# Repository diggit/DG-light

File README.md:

# DG-light

Lightweight module to iluminate various flying discs. (frisbee, DiscGolf,...? )

## Hardware

Kept simple and lightweight as possible. Only: MCU, leds, button, passives.
- **MCU**: **ATMEGA8A**
- **LEDs**:
 - 16x 5mm edge oriented LEDs
 - 1x SMD status LED
- **Buttons**:
 - user button (all settings)
 - reset button (wake from power off)

## V1
Proof of concept. Partialy worked.
### problems:
- **SW**: needed recalibration often (changing surfaces like: grass and asphalt caused capacity changes)
- **HW**:
 - missing charging port 
 - missing battery connect jumper
 - ISP inder battery
*sensitive to palm under electronics -> used as another control element (reset after pickup)*

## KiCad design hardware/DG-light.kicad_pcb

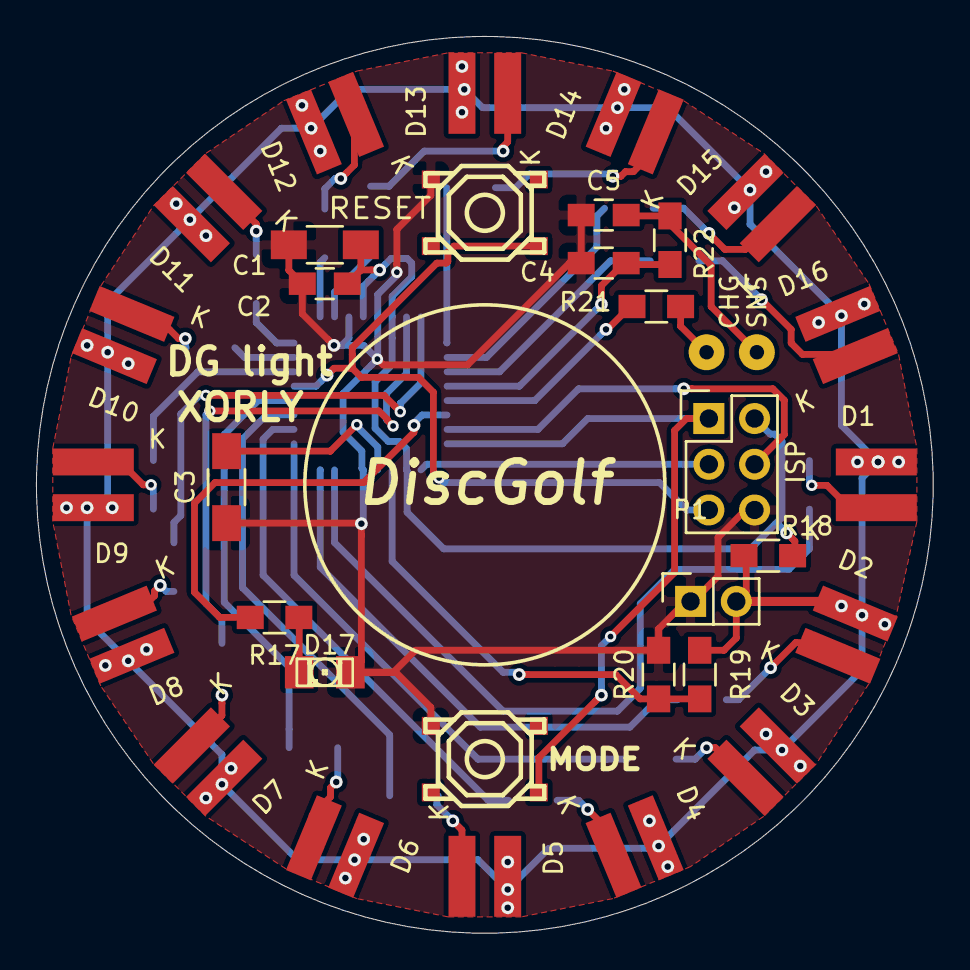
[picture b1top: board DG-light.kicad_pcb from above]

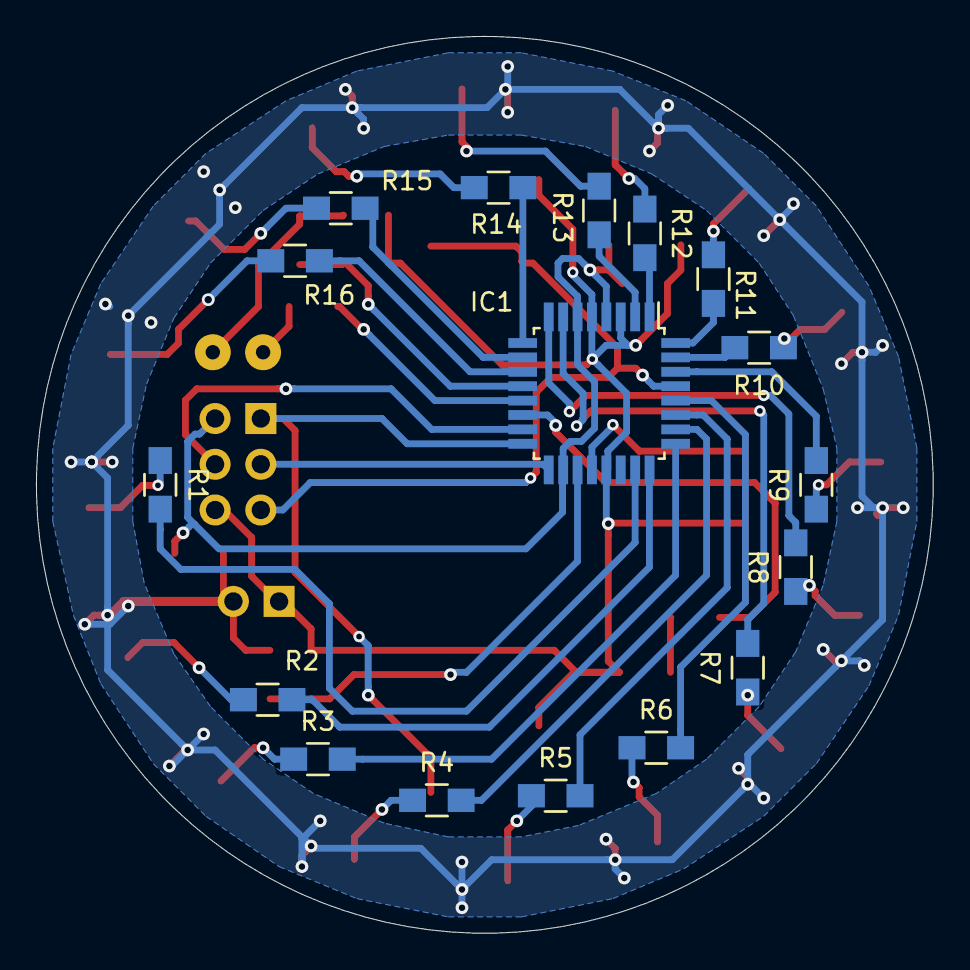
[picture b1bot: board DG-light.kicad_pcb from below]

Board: 2 copper layers, 49.8 x 49.8 mm, 51 parts (17 on the bottom side), 47 nets.

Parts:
C1, C3: C; C_1206_HandSoldering
C2, C4, C5: C; C_0805_HandSoldering
CHG: C_CHARGE; SolderWirePad_single_0-8mmDrill
D1, D2, D3, D4, D5, D6, D7, D8, D9, D10, D11, D12, D13, D14, D15, D16: LED; LED-5MM-SMD
D17: LED; LED-1206
IC1: ATMEGA8-AI; TQFP-32_7x7mm_Pitch0.8mm
ISP: ISP; Pin_Header_Straight_2x03
P1: PWR; Pin_Header_Straight_2x01
R1, R2, R3, R4, R5, R6, R7, R8, R9, R10, R11, R12, R13, R14, R15, R16, R17, R18, R21, R22: R; R_0805_HandSoldering
R19: R_SNS_HIGH; R_0805_HandSoldering
R20: R_SNS_LOW; R_0805_HandSoldering
SNS: C_SNS; SolderWirePad_single_0-8mmDrill
SW1: MODE; smd_push2
SW2: RESET; smd_push2

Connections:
+BATT: D1.1, D2.1, D3.1, D4.1, D5.1, D6.1, D7.1, D8.1, D9.1, D10.1, D11.1, D12.1, D13.1, D14.1, D15.1, D16.1, P1.2, R18.2, R19.2
C_SNS: C4.1, IC1.12, R22.2
GND: C1.2, C2.2, C3.1, C4.2, C5.2, D17.2, IC1.3, IC1.5, IC1.21, ISP.6, P1.1, R20.1, SW1.1, SW2.1
unnamed: C3.2, IC1.20
unnamed: C5.1, R22.1, SNS.1
unnamed: D1.2, R1.1
unnamed: D2.2, R2.1
unnamed: D3.2, R3.1
unnamed: D4.2, R4.1
unnamed: D5.2, R5.1
unnamed: D6.2, R6.1
unnamed: D7.2, R7.1
unnamed: D8.2, R8.1
unnamed: D9.2, R9.1
unnamed: D10.2, R10.1
unnamed: D11.2, R11.1
unnamed: D12.2, R12.1
unnamed: D13.2, R13.1
unnamed: D14.2, R14.1
unnamed: D15.2, R15.1
unnamed: D16.2, R16.1
unnamed: D17.1, R17.1
unnamed: IC1.1, R12.2
unnamed: IC1.2, R13.2
unnamed: IC1.7, R7.2
unnamed: IC1.8, R8.2
unnamed: IC1.9, R14.2
unnamed: IC1.10, R15.2
unnamed: IC1.11, R16.2
unnamed: IC1.13, R21.2
unnamed: IC1.14, R17.2
unnamed: IC1.15, ISP.4
unnamed: IC1.16, ISP.1, SW1.2
unnamed: IC1.17, ISP.3
unnamed: IC1.23, R1.2
unnamed: IC1.24, R2.2
unnamed: IC1.25, R3.2
unnamed: IC1.26, R4.2
unnamed: IC1.27, R5.2
unnamed: IC1.28, R6.2
unnamed: IC1.30, R9.2
unnamed: IC1.31, R10.2
unnamed: IC1.32, R11.2
unnamed: CHG.1, R21.1
RST: IC1.29, ISP.5, SW2.2
VCC: C1.1, C2.1, IC1.4, IC1.6, IC1.18, ISP.2, R18.1
V_SNS: IC1.19, R19.1, R20.2

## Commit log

2016-08-19 Initial commit - hardware - PCB v1 (old, need rework) - sch slightly improved, not matching PCB
    - code v1
2016-08-19 Add README.md
